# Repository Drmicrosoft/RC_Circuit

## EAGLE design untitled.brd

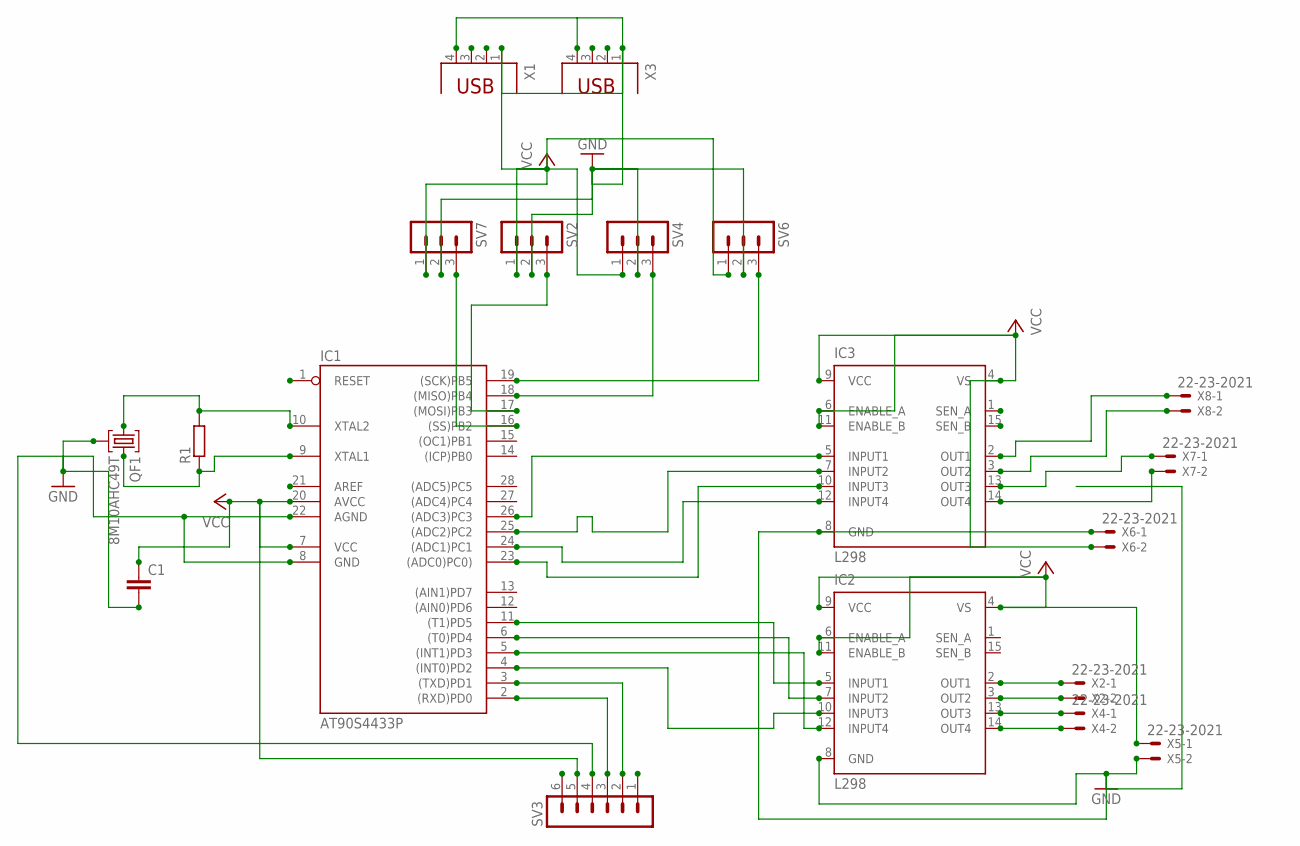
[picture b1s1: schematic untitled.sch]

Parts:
C1: C2,5-3; C2.5-3
IC1: AT90S4433P; DIL28-3
IC2, IC3: L298; MULTIWATT-15
QF1: 8M10AHC49T; HC49U
R1: R0207/10; 0207/10
SV2, SV4, SV6, SV7: MA03-1
SV3: MA06-1
X1, X3: PN61729
X2, X4, X5, X6, X7, X8: 22-23-2021

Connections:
GND: C1.2, IC1.8 (GND), IC1.22 (AGND), IC2.8 (GND), IC3.8 (GND), QF1.2, SV2.2, SV3.4, SV4.2, SV6.2, SV7.2, X1.4, X3.4, X5.2, X6.1
unnamed: IC1.10 (XTAL2), QF1.1, R1.2
unnamed: IC1.18 ((MISO)PB4), SV4.3
unnamed: IC1.23 ((ADC0)PC0)), IC3.10 (INPUT3)
unnamed: IC1.16 ((SS)PB2), SV7.3
unnamed: IC1.9 (XTAL1), QF1.3, R1.1
unnamed: IC1.17 ((MOSI)PB3), SV2.3
unnamed: IC2.2 (OUT1), X2.1
unnamed: IC1.26 ((ADC3)PC3), IC3.5 (INPUT1)
unnamed: IC1.19 ((SCK)PB5), SV6.3
unnamed: IC1.24 ((ADC1)PC1), IC3.12 (INPUT4)
unnamed: IC2.3 (OUT2), X2.2
unnamed: IC1.25 ((ADC2)PC2), IC3.7 (INPUT2)
unnamed: IC2.13 (OUT3), X4.1
unnamed: IC2.14 (OUT4), X4.2
unnamed: IC1.4 ((INT0)PD2), IC2.10 (INPUT3)
unnamed: IC1.11 ((T1)PD5), IC2.5 (INPUT1)
unnamed: IC1.6 ((T0)PD4), IC2.7 (INPUT2)
unnamed: IC1.5 ((INT1)PD3), IC2.12 (INPUT4)
unnamed: IC3.2 (OUT1), X8.1
unnamed: IC3.3 (OUT2), X8.2
unnamed: IC3.13 (OUT3), X7.1
unnamed: IC3.14 (OUT4), X7.2
unnamed: IC1.2 ((RXD)PD0), SV3.3
unnamed: IC1.3 ((TXD)PD1), SV3.2
VCC: C1.1, IC1.7 (VCC), IC1.20 (AVCC), IC2.4 (VS), IC2.6 (ENABLE_A), IC2.9 (VCC), IC2.11 (ENABLE_B), IC3.4 (VS), IC3.6 (ENABLE_A), IC3.9 (VCC), IC3.11 (ENABLE_B), SV2.1, SV3.5, SV4.1, SV6.1, SV7.1, X1.1, X3.1, X5.1, X6.2

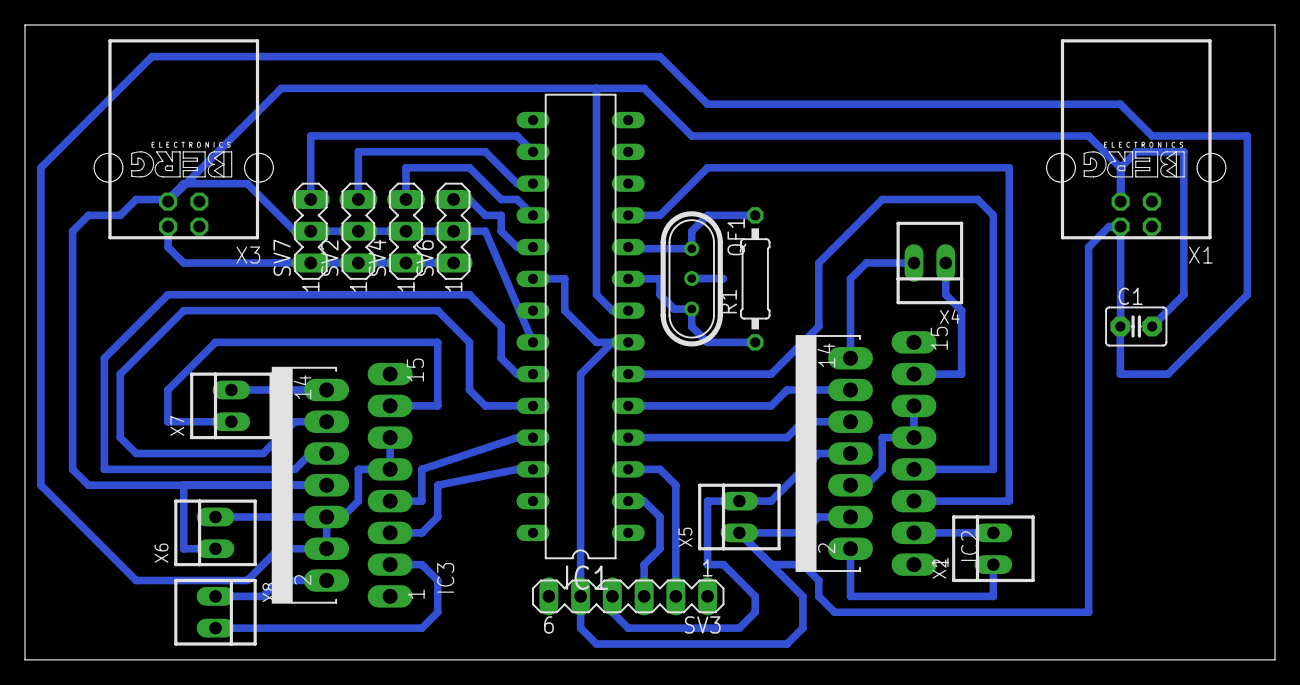
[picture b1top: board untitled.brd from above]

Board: 2 copper layers, 100.0 x 50.8 mm, 19 parts (0 on the bottom side), 26 nets.
